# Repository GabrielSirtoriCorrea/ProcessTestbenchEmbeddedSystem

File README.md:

# ProcessTestbenchEmbeddedSystem
Embedded system for control a Process Testbench

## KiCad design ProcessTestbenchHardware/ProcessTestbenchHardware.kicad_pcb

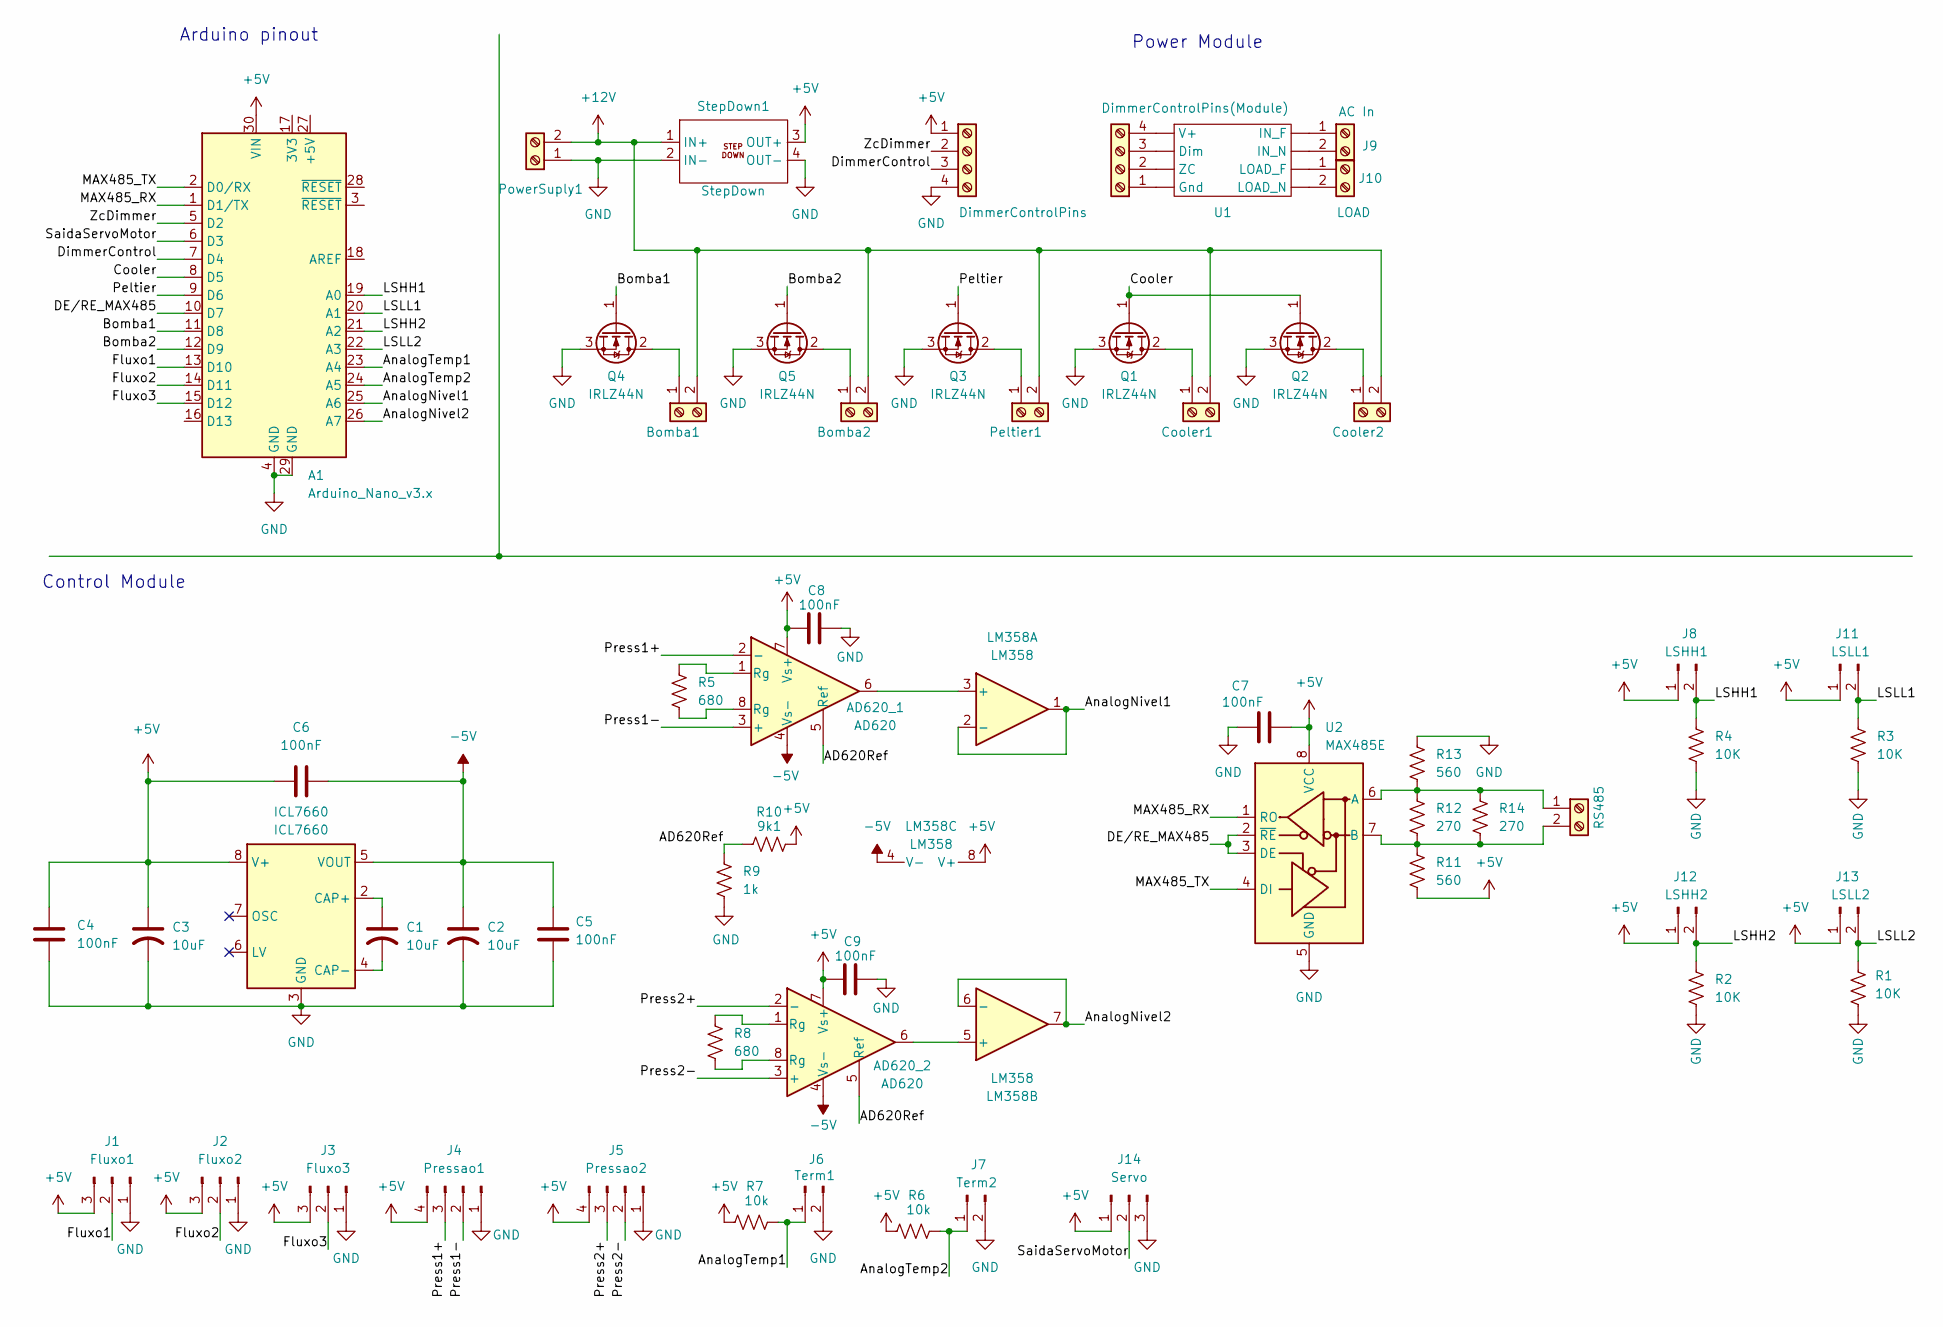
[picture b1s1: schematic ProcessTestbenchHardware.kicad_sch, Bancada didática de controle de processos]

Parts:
A1: Arduino_Nano_v3.x; Arduino_Nano
AD620_1, AD620_2: AD620; DIP-8_W7.62mm
Bomba1: Bomba1; TerminalBlock_Phoenix_MKDS-1,5-2-5.08_1x02_P5.08mm_Horizont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
Bomba2: Bomba2; TerminalBlock_Phoenix_MKDS-1,5-2-5.08_1x02_P5.08mm_Horizont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
C1, C2, C3: 10uF; C_Radial_D5.0mm_H7.0mm_P2.00mm
C4, C5, C6, C7, C8, C9: 100nF; C_Disc_D3.0mm_W1.6mm_P2.50mm
Cooler1: Cooler1; TerminalBlock_Phoenix_MKDS-1,5-2-5.08_1x02_P5.08mm_Horizont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
Cooler2: Cooler2; TerminalBlock_Phoenix_MKDS-1,5-2-5.08_1x02_P5.08mm_Horizont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
DimmerControlPins1: DimmerControlPins; TerminalBlock_Phoenix_MKDS-1,5-4-5.08_1x04_P5.08mm_Horizont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
DimmerControlPins2: DimmerControlPins(Module); TerminalBlock_Phoenix_MKDS-1,5-4-5.08_1x04_P5.08mm_Horizont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
ICL7660: ICL7660; DIP-8_W7.62mm
J1: Fluxo1; PinHeader_1x03_P2.54mm_Horizontal
J2: Fluxo2; PinHeader_1x03_P2.54mm_Horizontal
J3: Fluxo3; PinHeader_1x03_P2.54mm_Horizontal
J4: Pressao1; PinHeader_1x04_P2.54mm_Horizontal
J5: Pressao2; PinHeader_1x04_P2.54mm_Horizontal
J6: Term1; PinHeader_1x02_P2.54mm_Horizontal
J7: Term2; PinHeader_1x02_P2.54mm_Horizontal
J8: LSHH1; PinHeader_1x02_P2.54mm_Horizontal
J9: AC In; TerminalBlock_MaiXu_MX126-5.0-02P_1x02_P5.00mm
J10: LOAD; TerminalBlock_MaiXu_MX126-5.0-02P_1x02_P5.00mm
J11: LSLL1; PinHeader_1x02_P2.54mm_Horizontal
J12: LSHH2; PinHeader_1x02_P2.54mm_Horizontal
J13: LSLL2; PinHeader_1x02_P2.54mm_Horizontal
J14: Servo; PinHeader_1x03_P2.54mm_Horizontal
LM358: LM358; DIP-8_W7.62mm
Peltier1: Peltier1; TerminalBlock_Phoenix_MKDS-1,5-2-5.08_1x02_P5.08mm_Horizont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
PowerSuply1: PowerSuply; TerminalBlock_Phoenix_MKDS-1,5-2-5.08_1x02_P5.08mm_Horizont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
Q1, Q2, Q3, Q4, Q5: IRLZ44N; TO-220-3_Vertical
R1, R2, R3, R4: 10K; R_Axial_DIN0207_L6.3mm_D2.5mm_P7.62mm_Horizontal
R5, R8: 680; R_Axial_DIN0207_L6.3mm_D2.5mm_P7.62mm_Horizontal
R6, R7: 10k; R_Axial_DIN0207_L6.3mm_D2.5mm_P7.62mm_Horizontal
R9: 1k; R_Axial_DIN0207_L6.3mm_D2.5mm_P7.62mm_Horizontal
R10: 9k1; R_Axial_DIN0207_L6.3mm_D2.5mm_P7.62mm_Horizontal
R11, R13: 560; R_Axial_DIN0207_L6.3mm_D2.5mm_P7.62mm_Horizontal
R12, R14: 270; R_Axial_DIN0207_L6.3mm_D2.5mm_P7.62mm_Horizontal
RS485: RS485; TerminalBlock_Phoenix_MKDS-1,5-2-5.08_1x02_P5.08mm_Horizont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
StepDown1: StepDown; SRT_MPT1584EN_Module
U1: (no value)
U2: MAX485E; DIP-8_W7.62mm

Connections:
+5V: A1.30 (VIN), AD620_1.7 (Vs+), AD620_2.7 (Vs+), C3.1, C4.1, C6.1, C7.2, C8.2, C9.2, DimmerControlPins1.1, ICL7660.8 (V+), J1.3, J2.3, J3.3, J4.4, J5.4, J8.1, J11.1, J12.1, J13.1, J14.1, LM358.8 (V+), R6.1, R7.1, R10.2, R11.1, StepDown1.3 (OUT+), U2.8 (VCC)
+12V: Bomba1.2, Bomba2.2, Cooler1.2, Cooler2.2, Peltier1.2, PowerSuply1.2, StepDown1.1 (IN+)
-5V: AD620_1.4 (Vs-), AD620_2.4 (Vs-), C2.1, C5.1, C6.2, ICL7660.5 (VOUT), LM358.4 (V-)
/AD620Ref: AD620_1.5 (Ref), AD620_2.5 (Ref), R9.2, R10.1
/AnalogNivel1: A1.25 (A6), LM358.1, LM358.2 (-)
/AnalogNivel2: A1.26 (A7), LM358.6 (-), LM358.7
/AnalogTemp1: A1.23 (A4), J6.1, R7.2
/AnalogTemp2: A1.24 (A5), J7.1, R6.2
/Bomba1: A1.11 (D8), Q4.1 (G)
/Bomba2: A1.12 (D9), Q5.1 (G)
/Cooler: A1.8 (D5), Q1.1 (G), Q2.1 (G)
/DE/RE_MAX485: A1.10 (D7), U2.2 (~RE), U2.3 (DE)
/DimmerControl: A1.7 (D4), DimmerControlPins1.3
/Fluxo1: A1.13 (D10), J1.2
/Fluxo2: A1.14 (D11), J2.2
/Fluxo3: A1.15 (D12), J3.2
/LSHH1: A1.19 (A0), J8.2, R4.1
/LSHH2: A1.21 (A2), J12.2, R2.1
/LSLL1: A1.20 (A1), J11.2, R3.1
/LSLL2: A1.22 (A3), J13.2, R1.1
/MAX485_RX: A1.1 (D1/TX), U2.1 (RO)
/MAX485_TX: A1.2 (D0/RX), U2.4 (DI)
/Peltier: A1.9 (D6), Q3.1 (G)
/Press1+: AD620_1.2 (-), J4.3
/Press1-: AD620_1.3 (+), J4.2
/Press2+: AD620_2.2 (-), J5.3
/Press2-: AD620_2.3 (+), J5.2
/SaidaServoMotor: A1.6 (D3), J14.2
/ZcDimmer: A1.5 (D2), DimmerControlPins1.2
GND: A1.4 (GND), A1.29 (GND), C2.2, C3.2, C4.2, C5.2, C7.1, C8.1, C9.1, DimmerControlPins1.4, ICL7660.3 (GND), J1.1, J2.1, J3.1, J4.1, J5.1, J6.2, J7.2, J14.3, PowerSuply1.1, Q1.3 (S), Q2.3 (S), Q3.3 (S), Q4.3 (S), Q5.3 (S), R1.2, R2.2, R3.2, R4.2, R9.1, R13.2, StepDown1.2 (IN-), StepDown1.4 (OUT-), U2.5 (GND)
unnamed: AD620_1.1 (Rg), R5.1
unnamed: AD620_1.8 (Rg), R5.2
unnamed: AD620_2.1 (Rg), R8.1
unnamed: AD620_2.8 (Rg), R8.2
unnamed: Bomba1.1, Q4.2 (D)
unnamed: Bomba2.1, Q5.2 (D)
unnamed: Cooler1.1, Q1.2 (D)
unnamed: Cooler2.1, Q2.2 (D)
unnamed: DimmerControlPins2.1, U1.
unnamed: DimmerControlPins2.2, U1.
unnamed: DimmerControlPins2.3, U1.
unnamed: DimmerControlPins2.4, U1.
unnamed: C1.1, ICL7660.2 (CAP+)
unnamed: C1.2, ICL7660.4 (CAP-)
unnamed: J9.1, U1.
unnamed: J9.2, U1.
unnamed: J10.1, U1.
unnamed: J10.2, U1.
unnamed: AD620_1.6, LM358.3 (+)
unnamed: AD620_2.6, LM358.5 (+)
unnamed: Peltier1.1, Q3.2 (D)
unnamed: R12.2, R13.1, R14.2, RS485.1, U2.6 (A)
unnamed: R11.2, R12.1, R14.1, RS485.2, U2.7 (B)

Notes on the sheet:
Arduino pinout
Power Module
Control Module

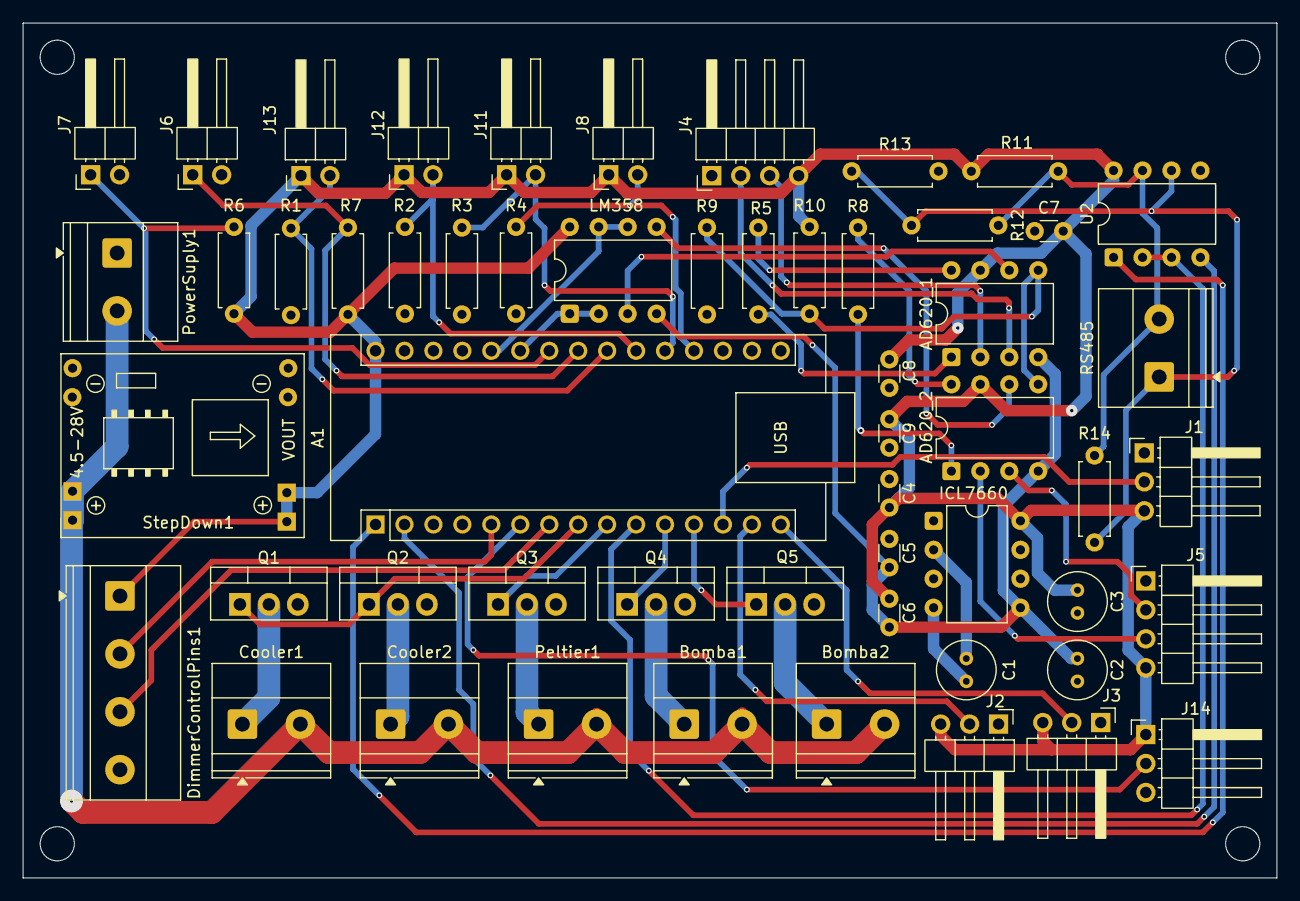
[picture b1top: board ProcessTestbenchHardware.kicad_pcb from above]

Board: 2 copper layers, 110.0 x 75.0 mm, 55 parts (0 on the bottom side), 45 nets.
